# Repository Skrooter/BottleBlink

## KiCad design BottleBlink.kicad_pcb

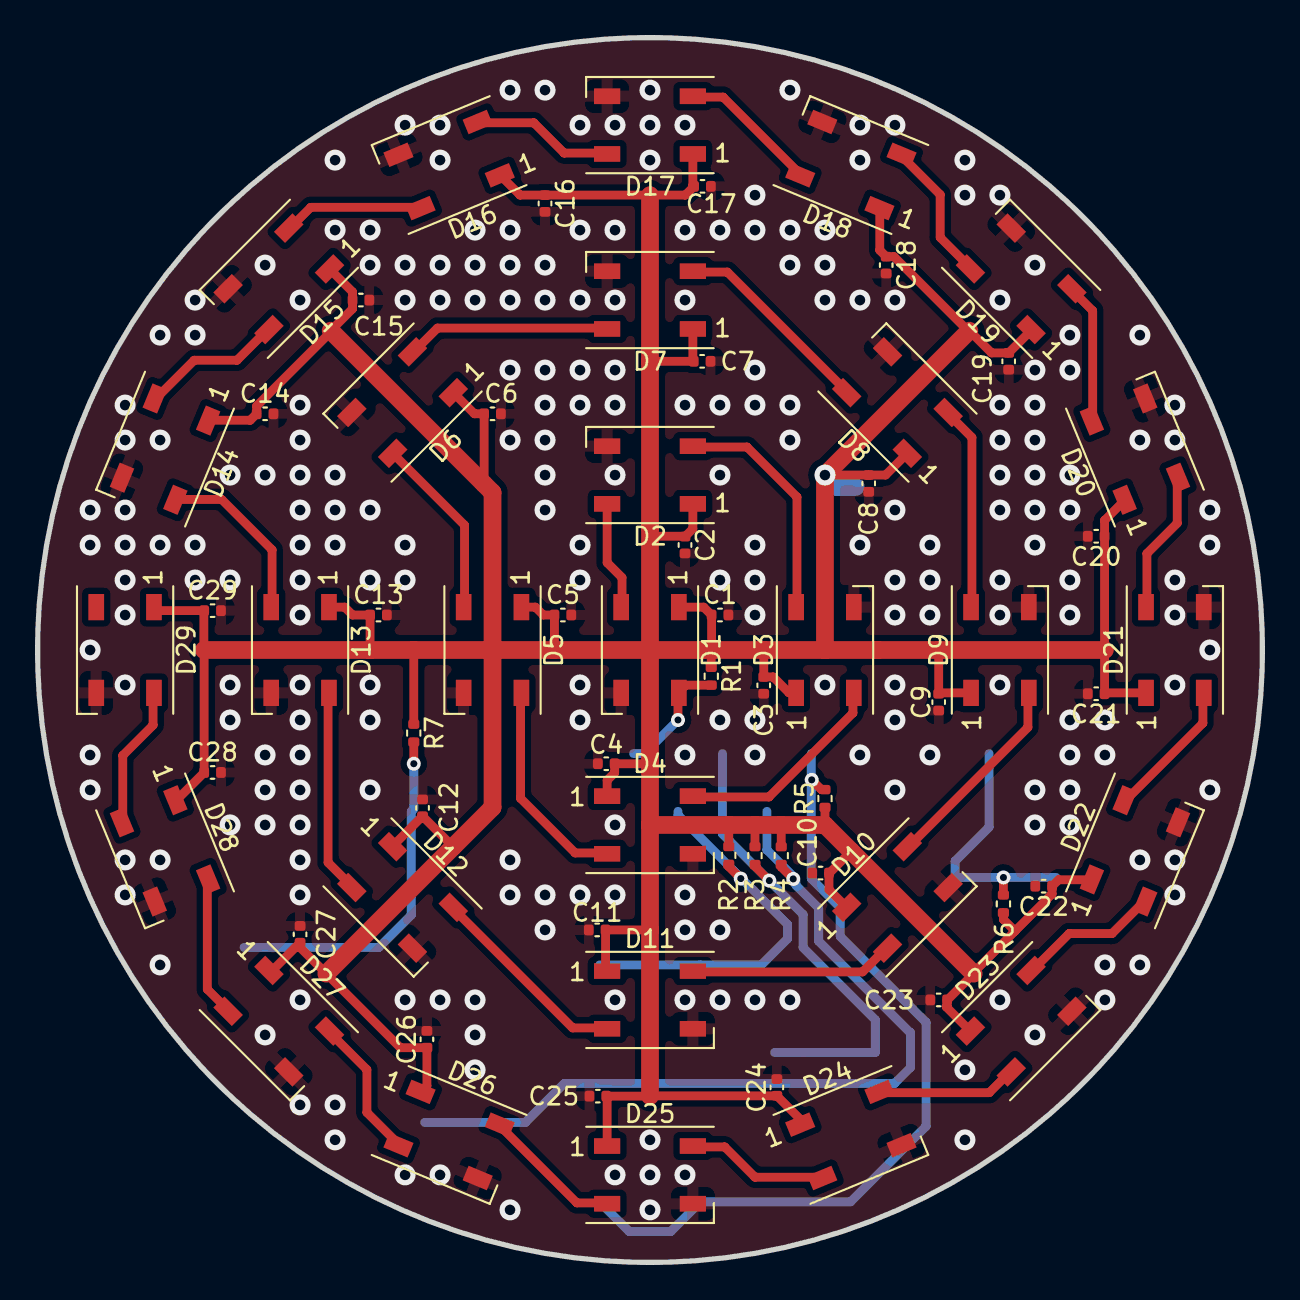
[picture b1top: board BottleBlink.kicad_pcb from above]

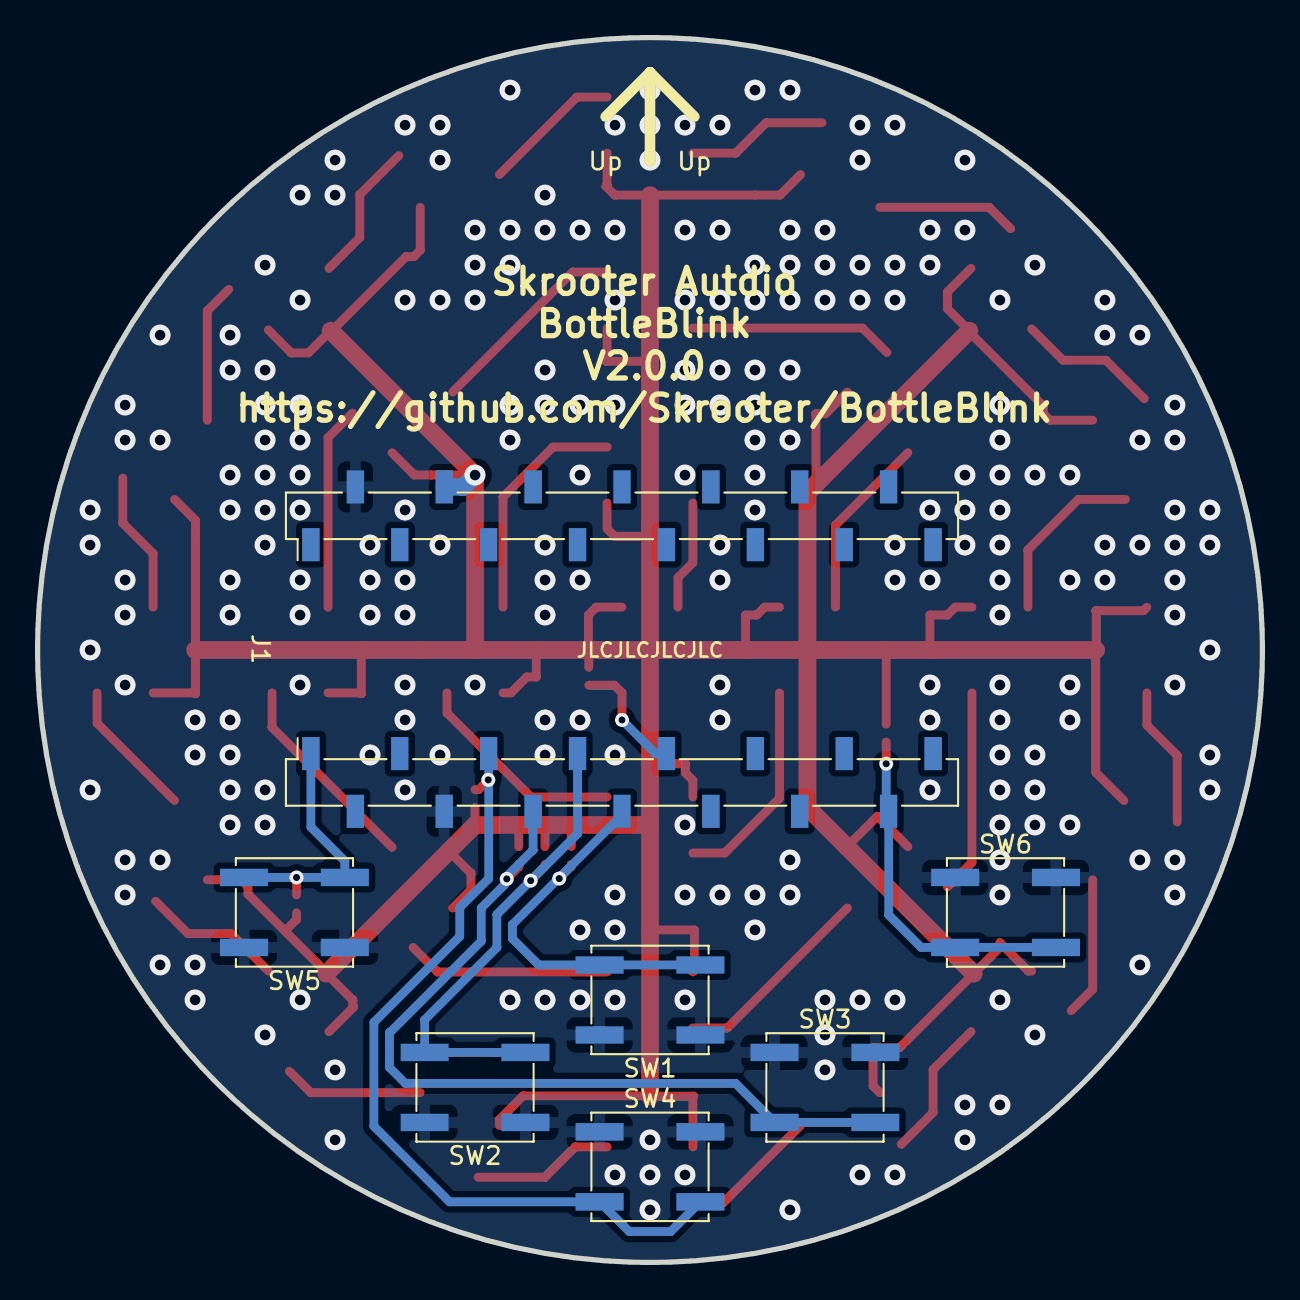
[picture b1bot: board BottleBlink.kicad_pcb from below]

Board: 2 copper layers, 70.0 x 70.0 mm, 72 parts (7 on the bottom side), 37 nets.

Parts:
C1, C2, C3, C4, C5, C6, C7, C8, C9, C10, C11, C12, C13, C14, C15, C16, C17, C18, C19, C20, C21, C22, C23, C24, C25, C26, C27, C28, C29: 1u; C_0402_1005Metric
D1, D2, D3, D4, D5, D6, D7, D8, D9, D10, D11, D12, D13, D14, D15, D16, D17, D18, D19, D20, D21, D22, D23, D24, D25, D26, D27, D28, D29: WS2812B; LED_WS2812B_PLCC4_5.0x5.0mm_P3.2mm
J1: Arduino_Nano_v2.x; ArduinoNanoSMD
R1: 1k; R_0402_1005Metric
R2, R3, R4, R5, R6, R7: 10k; R_0402_1005Metric
SW1, SW2, SW3, SW4, SW5, SW6: SW_DPST_x2; SW_SPST_EVQP0

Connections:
+5V: C1.1, C2.1, C3.1, C4.1, C5.1, C6.1, C7.1, C8.1, C9.1, C10.1, C11.1, C12.1, C13.1, C14.1, C15.1, C16.1, C17.1, C18.1, C19.1, C20.1, C21.1, C22.1, C23.1, C24.1, C25.1, C26.1, C27.1, C28.1, C29.1, D1.1 (VDD), D2.1 (VDD), D3.1 (VDD), D4.1 (VDD), D5.1 (VDD), D6.1 (VDD), D7.1 (VDD), D8.1 (VDD), D9.1 (VDD), D10.1 (VDD), D11.1 (VDD), D12.1 (VDD), D13.1 (VDD), D14.1 (VDD), D15.1 (VDD), D16.1 (VDD), D17.1 (VDD), D18.1 (VDD), D19.1 (VDD), D20.1 (VDD), D21.1 (VDD), D22.1 (VDD), D23.1 (VDD), D24.1 (VDD), D25.1 (VDD), D26.1 (VDD), D27.1 (VDD), D28.1 (VDD), D29.1 (VDD), J1.27 (+5V), R1.1, R2.1, R3.1, R4.1, R5.1, R6.1, R7.1
/Btn1: J1.8 (D5), R2.2, SW1.2 (B)
/Btn2: J1.7 (D4), R3.2, SW2.2 (B)
/Btn3: J1.6 (D3), R4.2, SW3.2 (B)
/Btn4: J1.5 (D2), R5.2, SW4.2 (B)
/Btn5: J1.1 (D1/TX), R6.2, SW5.2 (B)
/Btn6: J1.14 (D11), R7.2, SW6.2 (B)
/LedIn: D1.4 (DIN), J1.9 (D6), R1.2
GND: C1.2, C2.2, C3.2, C4.2, C5.2, C6.2, C7.2, C8.2, C9.2, C10.2, C11.2, C12.2, C13.2, C14.2, C15.2, C16.2, C17.2, C18.2, C19.2, C20.2, C21.2, C22.2, C23.2, C24.2, C25.2, C26.2, C27.2, C28.2, C29.2, D1.3 (VSS), D2.3 (VSS), D3.3 (VSS), D4.3 (VSS), D5.3 (VSS), D6.3 (VSS), D7.3 (VSS), D8.3 (VSS), D9.3 (VSS), D10.3 (VSS), D11.3 (VSS), D12.3 (VSS), D13.3 (VSS), D14.3 (VSS), D15.3 (VSS), D16.3 (VSS), D17.3 (VSS), D18.3 (VSS), D19.3 (VSS), D20.3 (VSS), D21.3 (VSS), D22.3 (VSS), D23.3 (VSS), D24.3 (VSS), D25.3 (VSS), D26.3 (VSS), D27.3 (VSS), D28.3 (VSS), D29.3 (VSS), J1.4 (GND), J1.29 (GND), SW1.1 (A), SW2.1 (A), SW3.1 (A), SW4.1 (A), SW5.1 (A), SW6.1 (A)
unnamed: D1.2 (DOUT), D2.4 (DIN)
unnamed: D2.2 (DOUT), D3.4 (DIN)
unnamed: D3.2 (DOUT), D4.4 (DIN)
unnamed: D4.2 (DOUT), D5.4 (DIN)
unnamed: D5.2 (DOUT), D6.4 (DIN)
unnamed: D6.2 (DOUT), D7.4 (DIN)
unnamed: D7.2 (DOUT), D8.4 (DIN)
unnamed: D8.2 (DOUT), D9.4 (DIN)
unnamed: D9.2 (DOUT), D10.4 (DIN)
unnamed: D10.2 (DOUT), D11.4 (DIN)
unnamed: D11.2 (DOUT), D12.4 (DIN)
unnamed: D12.2 (DOUT), D13.4 (DIN)
unnamed: D13.2 (DOUT), D14.4 (DIN)
unnamed: D14.2 (DOUT), D15.4 (DIN)
unnamed: D15.2 (DOUT), D16.4 (DIN)
unnamed: D16.2 (DOUT), D17.4 (DIN)
unnamed: D17.2 (DOUT), D18.4 (DIN)
unnamed: D18.2 (DOUT), D19.4 (DIN)
unnamed: D19.2 (DOUT), D20.4 (DIN)
unnamed: D20.2 (DOUT), D21.4 (DIN)
unnamed: D21.2 (DOUT), D22.4 (DIN)
unnamed: D22.2 (DOUT), D23.4 (DIN)
unnamed: D23.2 (DOUT), D24.4 (DIN)
unnamed: D24.2 (DOUT), D25.4 (DIN)
unnamed: D25.2 (DOUT), D26.4 (DIN)
unnamed: D26.2 (DOUT), D27.4 (DIN)
unnamed: D27.2 (DOUT), D28.4 (DIN)
unnamed: D28.2 (DOUT), D29.4 (DIN)

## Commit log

2021-01-10 Initial commit with version 1.0.0 ready for review
2021-01-10 Remove unused files
2021-01-10 Remove old stepfile
2021-01-13 Add changes based on review comments
2021-01-15 Add LCSC numbers and QR code to PCB
2023-03-31 Update to rev2
    * Removed a lot of components, e.g. current and voltage measurements
    * Added a 1u cap for each LED
    * Added more buttons
    * Updated silk
2023-04-14 Final fixes before production
